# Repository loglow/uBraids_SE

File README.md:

# µBraids SE (uBraids, microBraids) Eurorack [Rev E]

## 8HP Eurorack module | Voltage-controlled digital oscillator

[µBraids SE](http://ubraids-se.com) is a voltage-controlled digital oscillator/sound source in 8HP with a wide range of creative and useful sound generation algorithms (aka models).

This re-engineered Eurorack module updates and simplifies the classic [Mutable Instruments Braids](https://mutable-instruments.net/modules/braids/) design with a custom brilliant orange LED display module protected by a clear acrylic lens, a low-profile rotary encoder, and an added attenuverter.

Fully compatible with upstream Braids firmware. Includes power cable, mounting hardware, and a one-year warranty. Designed and built with care by [Tall Dog Electronics](http://tall-dog.com) in Western Massachusetts. Licensed [CC BY-SA 4.0](https://creativecommons.org/licenses/by-sa/4.0/) open source hardware.

- **Height:** 3U (128.5 mm)
- **Width:** 8HP (40.3 mm)
- **Depth:** 31 mm (with power)
- **+12V:** 100 mA (average)
- **-12V:** 15 mA (average)

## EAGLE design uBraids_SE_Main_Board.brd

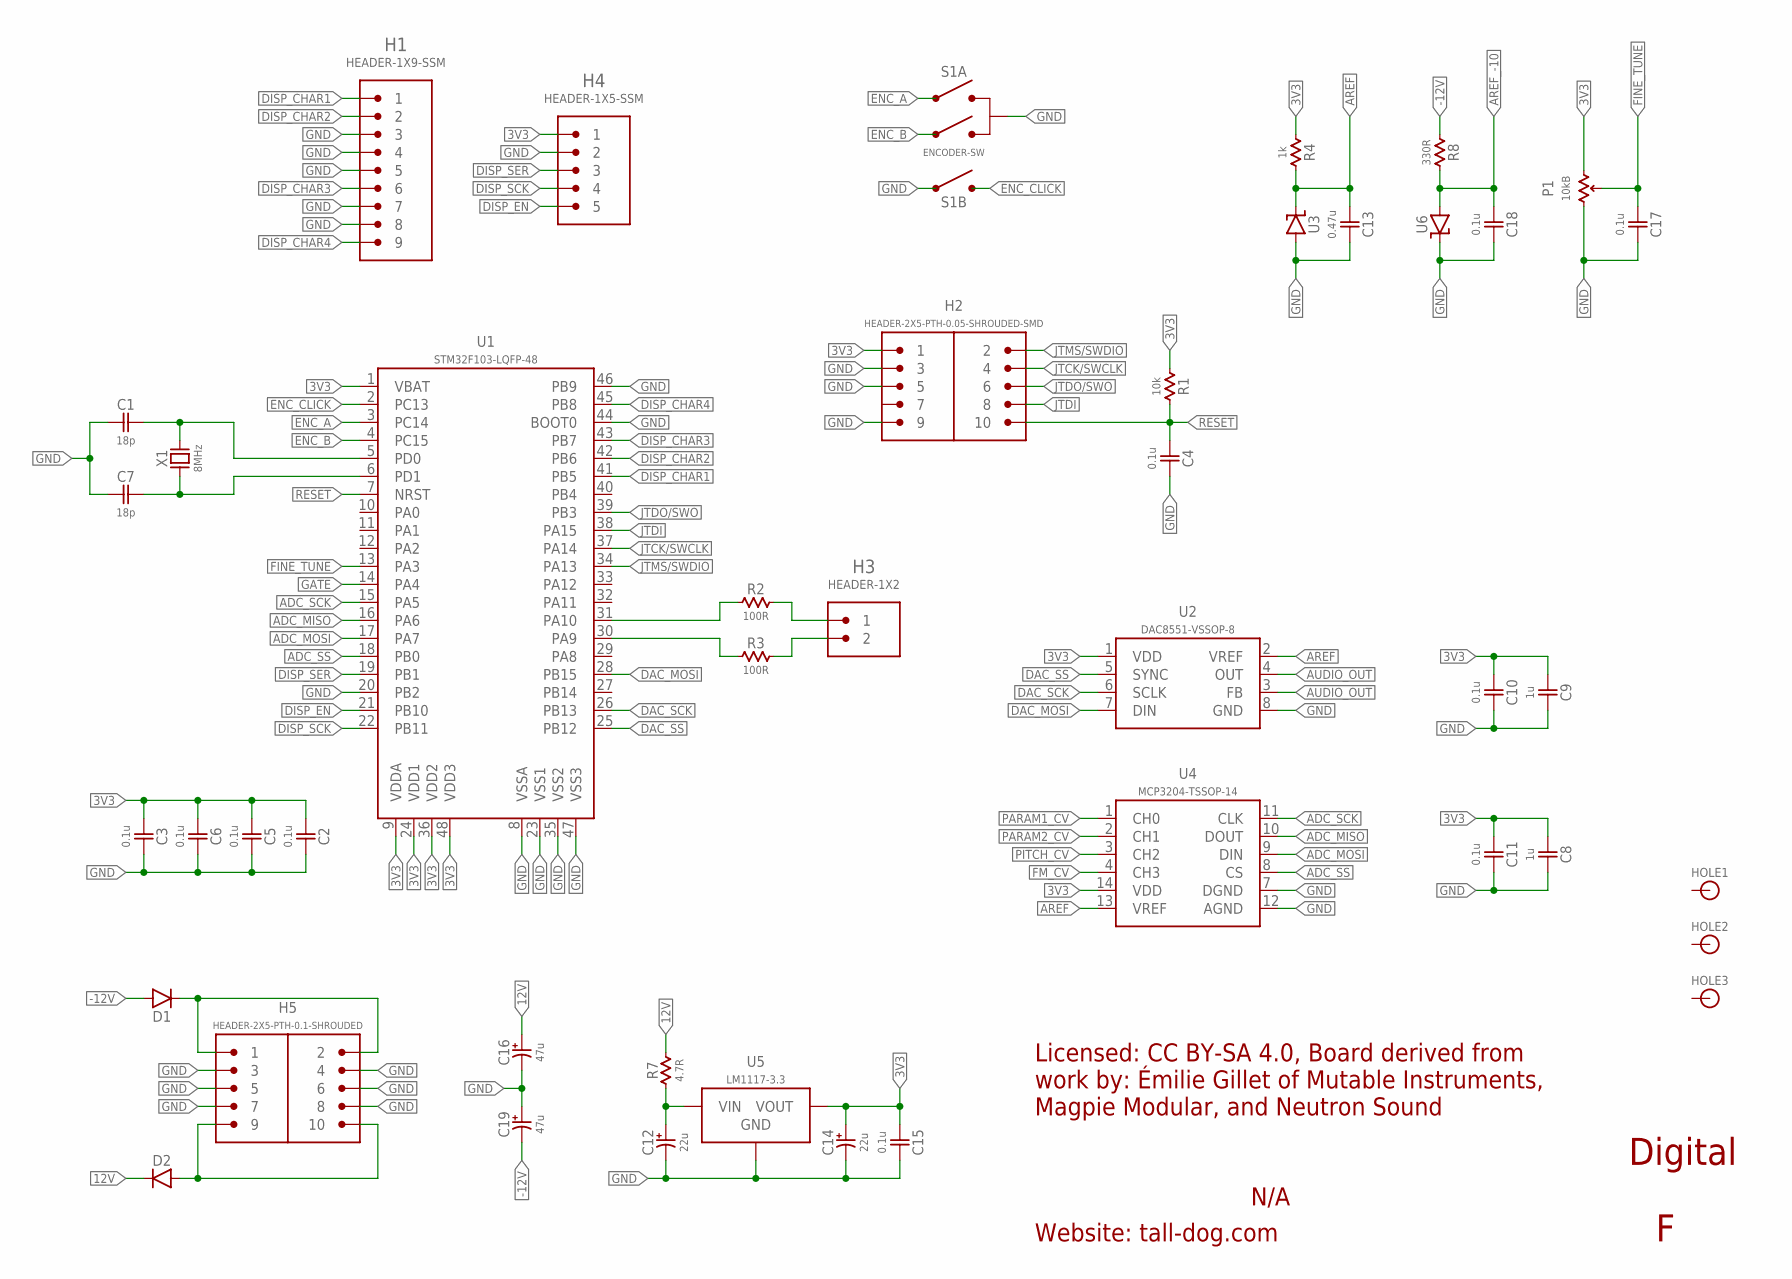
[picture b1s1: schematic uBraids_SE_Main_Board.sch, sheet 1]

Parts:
C1, C7: 18p; 0603-NP
C2, C3, C4, C5, C6, C10, C11, C15, C17, C18: 0.1u; 0603-NP
C8, C9: 1u; 0603-NP
C12, C14: 22u; ELECTRO-SMD-6.6MM
C13: 0.47u; 0603-NP
C16, C19: 47u; ELECTRO-SMD-6.6MM
D1, D2: 1N5819HW; SOD-123
H1: HEADER-1X9-SSM; SSM-109-S-SV-BE
H2: HEADER-2X5-PTH-0.05-SHROUDED-SMD; PTH-0.05-2X5-SHROUDED-SMD
H3: HEADER-1X2; PTH-0.1-1X2
H4: HEADER-1X5-SSM; SSM-105-S-SV-BE
H5: HEADER-2X5-PTH-0.1-SHROUDED; PTH-0.1-2X5-SHROUDED
HOLE1, HOLE2, HOLE3: HOLE; M2.5-HOLE
P1: 10kB; POT
R1: 10k; 0603-NP
R2, R3: 100R; 0603-NP
R4: 1k; 0603-NP
R7: 4.7R; 0805-NP
R8: 330R; 0805-NP
S1: ENCODER-SW; ENCODER-EC12E
U1: STM32F103-LQFP-48; LQFP-48
U2: DAC8551-VSSOP-8; VSSOP-8
U3: LM4040B25; SOT-23
U4: MCP3204-TSSOP-14; TSSOP-14
U5: LM1117-3.3; SOT-223
U6: LM4040B10; SOT-23
X1: 8MHz; CRYSTAL-ABM2

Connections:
3V3: C2.1, C3.1, C5.1, C6.1, C8.1, C9.1, C10.1, C11.1, C14.A (POS), C15.1, H2.1, H4.1, P1.P$1 (E), R1.1, R4.1, U1.1 (VBAT), U1.9 (VDDA), U1.24 (VDD1), U1.36 (VDD2), U1.48 (VDD3), U2.1 (VDD), U4.14 (VDD), U5.2 (VOUT), U5.4 (VOUT); also elsewhere on the board
12V: C16.A (POS), D2.C, R7.2; also elsewhere on the board
12V_BUS: D2.A, H5.9, H5.10
12V_U5: C12.A (POS), R7.1, U5.3 (VIN)
-12V: C19.C (NEG), D1.A, R8.1; also elsewhere on the board
-12V_BUS: D1.C, H5.1, H5.2
ADC_MISO: U1.16 (PA6), U4.10 (DOUT)
ADC_MOSI: U1.17 (PA7), U4.9 (DIN)
ADC_SCK: U1.15 (PA5), U4.11 (CLK)
ADC_SS: U1.18 (PB0), U4.8 (CS)
AREF: C13.1, R4.2, U2.2 (VREF), U3.1 (C), U4.13 (VREF)
AREF_-10: C18.1, R8.2, U6.2 (A); also elsewhere on the board
AUDIO_OUT: U2.3 (FB), U2.4 (OUT); also elsewhere on the board
DAC_MOSI: U1.28 (PB15), U2.7 (DIN)
DAC_SCK: U1.26 (PB13), U2.6 (SCLK)
DAC_SS: U1.25 (PB12), U2.5 (SYNC)
DISP_CHAR1: H1.1, U1.41 (PB5)
DISP_CHAR2: H1.2, U1.42 (PB6)
DISP_CHAR3: H1.6, U1.43 (PB7)
DISP_CHAR4: H1.9, U1.45 (PB8)
DISP_EN: H4.5, U1.21 (PB10)
DISP_SCK: H4.4, U1.22 (PB11)
DISP_SER: H4.3, U1.19 (PB1)
ENC_A: S1.B, U1.3 (PC14)
ENC_B: S1.A, U1.4 (PC15)
ENC_CLICK: S1.E (2), U1.2 (PC13)
FINE_TUNE: C17.1, P1.P$2 (S), U1.13 (PA3)
FM_CV: U4.4 (CH3); also elsewhere on the board
GATE: U1.14 (PA4); also elsewhere on the board
GND: C1.1, C2.2, C3.2, C4.2, C5.2, C6.2, C7.1, C8.2, C9.2, C10.2, C11.2, C12.C (NEG), C13.2, C14.C (NEG), C15.2, C16.C (NEG), C17.2, C18.2, C19.A (POS), H1.3, H1.4, H1.5, H1.7, H1.8, H2.3, H2.5, H2.9, H4.2, H5.3, H5.4, H5.5, H5.6, H5.7, H5.8, P1.P$3 (A), S1.C, S1.D (1), U1.8 (VSSA), U1.20 (PB2), U1.23 (VSS1), U1.35 (VSS2), U1.44 (BOOT0), U1.46 (PB9), U1.47 (VSS3), U2.8 (GND), U3.2 (A), U4.7 (DGND), U4.12 (AGND), U5.1 (GND), U6.1 (C); also elsewhere on the board
JTCK/SWCLK: H2.4, U1.37 (PA14)
JTDI: H2.8, U1.38 (PA15)
JTDO/SWO: H2.6, U1.39 (PB3)
JTMS/SWDIO: H2.2, U1.34 (PA13)
PARAM1_CV: U4.1 (CH0); also elsewhere on the board
PARAM2_CV: U4.2 (CH1); also elsewhere on the board
PD0-XTAL: C1.2, U1.5 (PD0), X1.2
PD1-XTAL: C7.2, U1.6 (PD1), X1.1
PITCH_CV: U4.3 (CH2); also elsewhere on the board
RESET: C4.1, H2.10, R1.2, U1.7 (NRST)
RX: H3.1, R2.2
RX_R: R2.1, U1.31 (PA10)
TX: H3.2, R3.2
TX_R: R3.1, U1.30 (PA9)

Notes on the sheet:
Licensed: CC BY-SA 4.0, Board derived from work by: Émilie Gillet of Mutable Instruments, Magpie Modular, and Neutron Sound
Website: tall-dog.com
N/A
Digital

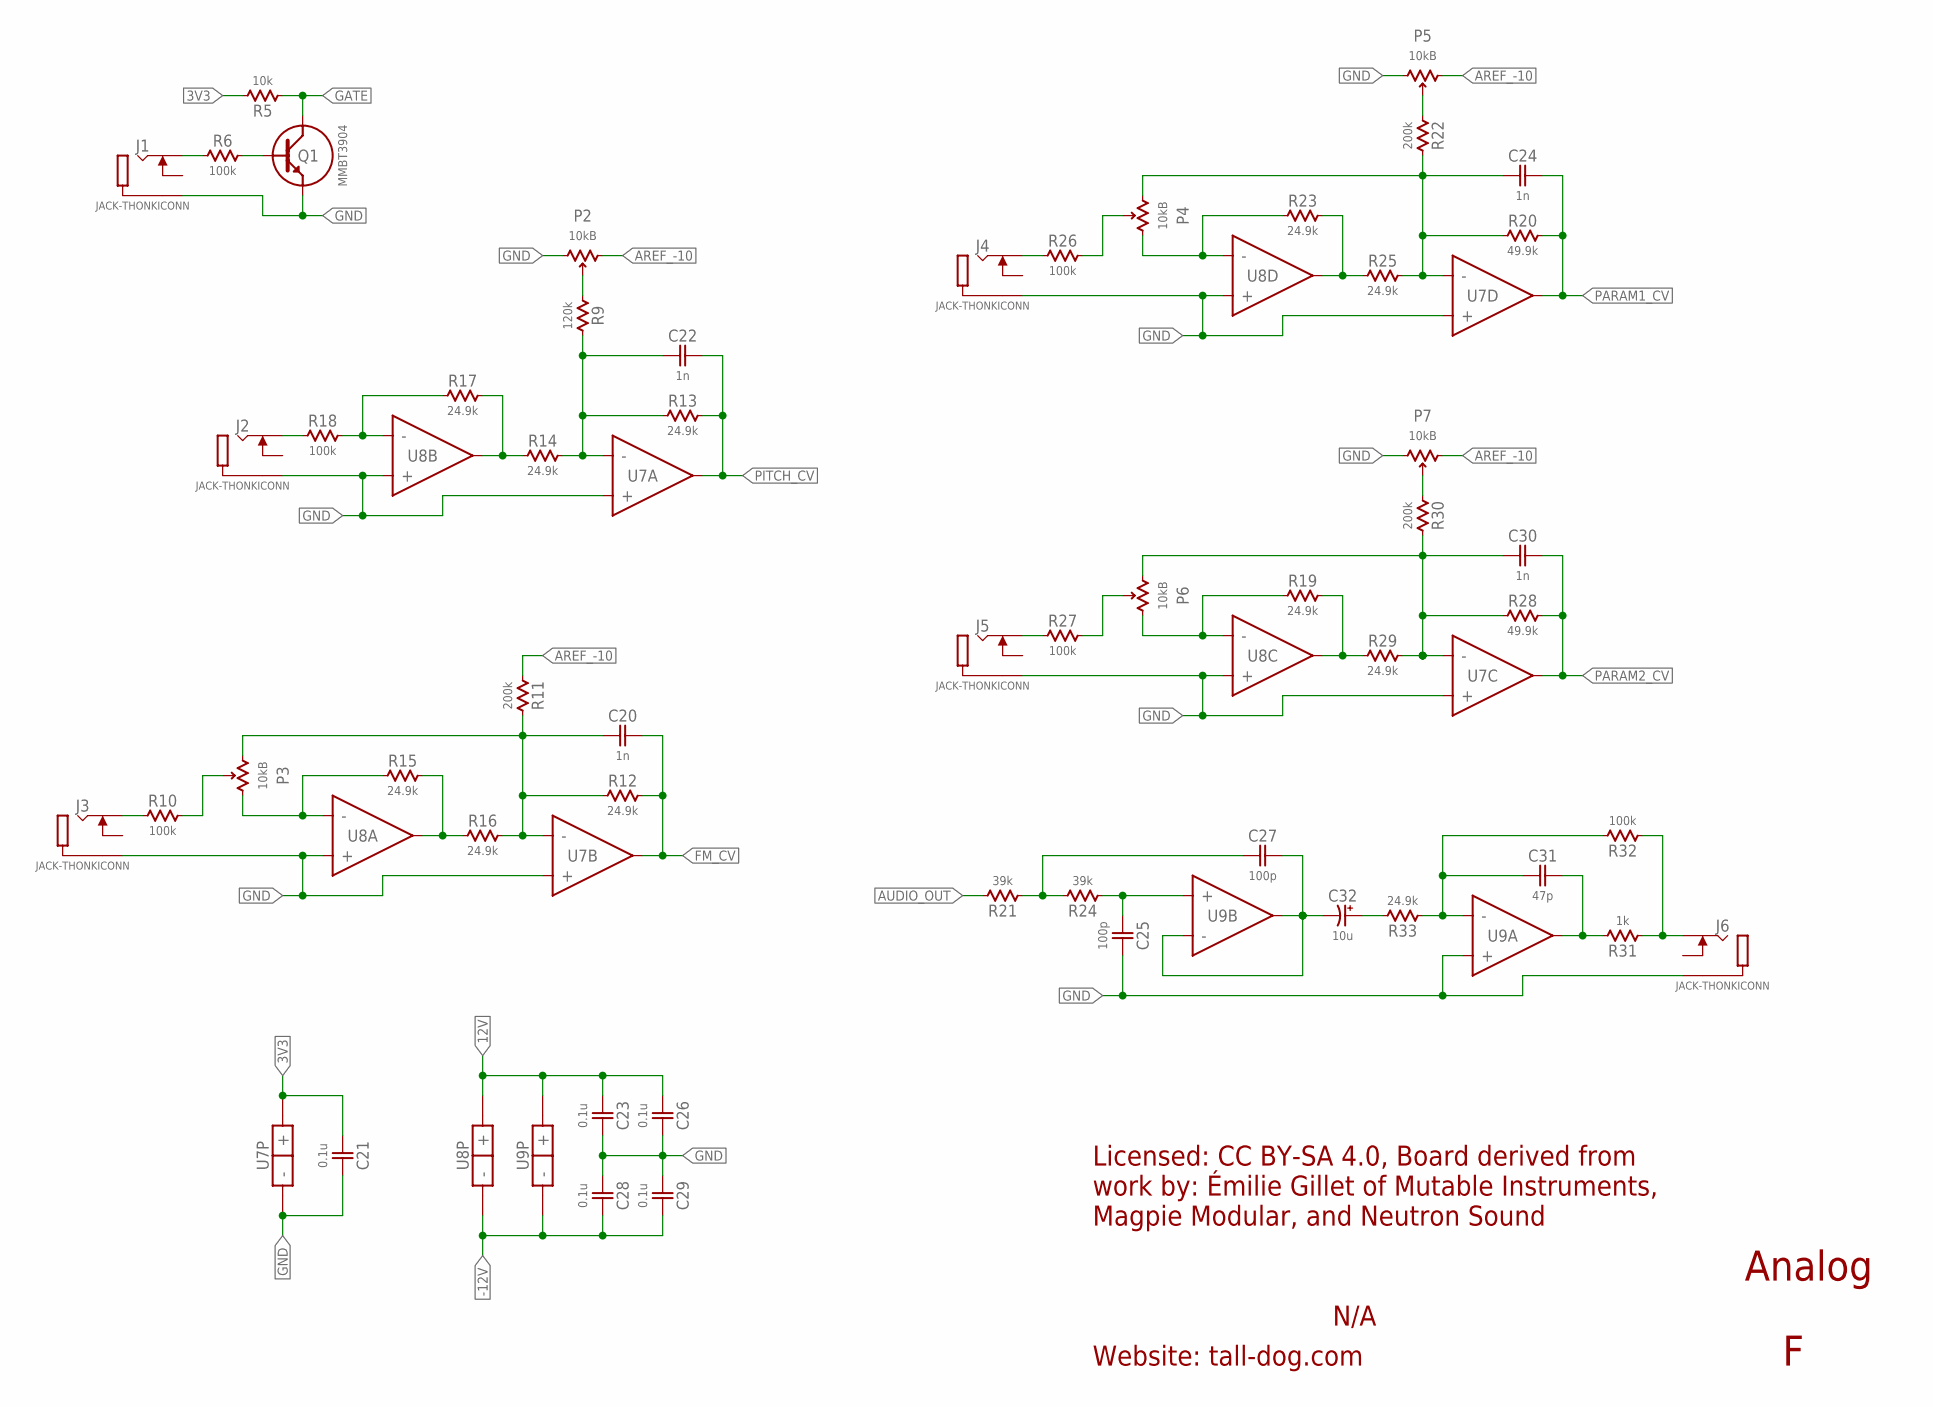
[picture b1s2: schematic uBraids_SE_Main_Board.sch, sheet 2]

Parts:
C20, C22, C24, C30: 1n; 0603-NP
C21, C23, C26, C28, C29: 0.1u; 0603-NP
C25, C27: 100p; 0603-NP
C31: 47p; 0603-NP
C32: 10u; ELECTRO-SMD-4.3MM
J1, J2, J3, J4, J5, J6: JACK-THONKICONN; THONKICONN
P2, P3, P4, P5, P6, P7: 10kB; POT
Q1: MMBT3904; SOT-23
R5: 10k; 0603-NP
R6, R10, R18, R26, R27, R32: 100k; 0603-NP
R9: 120k; 0603-NP
R11, R22, R30: 200k; 0603-NP
R12, R13, R14, R15, R16, R17, R19, R23, R25, R29, R33: 24.9k; 0603-NP
R20, R28: 49.9k; 0603-NP
R21, R24: 39k; 0603-NP
R31: 1k; 0603-NP
U7: MCP6004; TSSOP-14
U8: TL074-TSSOP-14; TSSOP-14
U9: TL072; TSSOP-8

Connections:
3V3: C21.1, R5.2, U7.4 (+); also elsewhere on the board
12V: C23.1, C26.1, U8.4 (+), U9.8 (+); also elsewhere on the board
-12V: C28.2, C29.2, U8.11 (-), U9.4 (-); also elsewhere on the board
AREF_-10: P2.P$1 (E), P5.P$1 (E), P7.P$1 (E), R11.1; also elsewhere on the board
AUDIO_OUT: R21.2; also elsewhere on the board
FM_CV: C20.2, R12.2, U7.7 (OUT); also elsewhere on the board
GATE: Q1.3 (C), R5.1; also elsewhere on the board
GND: C21.2, C23.2, C25.2, C26.2, C28.1, C29.1, J1.P1 (1), J2.P1 (1), J3.P1 (1), J4.P1 (1), J5.P1 (1), J6.P1 (1), P2.P$3 (A), P5.P$3 (A), P7.P$3 (A), Q1.2 (E), U7.3 (+), U7.5 (+), U7.10 (+), U7.11 (-), U7.12 (+), U8.3 (+), U8.5 (+), U8.10 (+), U8.12 (+), U9.3 (+); also elsewhere on the board
unnamed: P6.P$2 (S), R27.2
unnamed: C24.1, P4.P$3 (A), R20.1, R22.2, R25.2, U7.13 (-)
unnamed: R14.1, R17.2, U8.7 (OUT)
unnamed: P2.P$2 (S), R9.1
unnamed: J2.P3 (3), R18.1
unnamed: C22.1, R9.2, R13.1, R14.2, U7.2 (-)
unnamed: R17.1, R18.2, U8.6 (-)
unnamed: J3.P3 (3), R10.1
unnamed: J4.P3 (3), R26.1
unnamed: P3.P$2 (S), R10.2
unnamed: P4.P$1 (E), R23.1, U8.13 (-)
unnamed: R23.2, R25.1, U8.14 (OUT)
unnamed: P3.P$1 (E), R15.1, U8.2 (-)
unnamed: R15.2, R16.1, U8.1 (OUT)
unnamed: C20.1, P3.P$3 (A), R11.2, R12.1, R16.2, U7.6 (-)
unnamed: J1.P3 (3), R6.1
unnamed: R19.2, R29.1, U8.8 (OUT)
unnamed: J5.P3 (3), R27.1
unnamed: P5.P$2 (S), R22.1
unnamed: P4.P$2 (S), R26.2
unnamed: P6.P$1 (E), R19.1, U8.9 (-)
unnamed: P7.P$2 (S), R30.1
unnamed: Q1.1 (B), R6.2
unnamed: C27.2, C32.C (NEG), U9.6 (-), U9.7 (OUT)
unnamed: C32.A (POS), R33.2
unnamed: C25.1, R24.1, U9.5 (+)
unnamed: C30.1, P6.P$3 (A), R28.1, R29.2, R30.2, U7.9 (-)
unnamed: C27.1, R21.1, R24.2
unnamed: J6.P3 (3), R31.1, R32.1
unnamed: C31.2, R31.2, U9.1 (OUT)
unnamed: C31.1, R32.2, R33.1, U9.2 (-)
PARAM1_CV: C24.2, R20.2, U7.14 (OUT); also elsewhere on the board
PARAM2_CV: C30.2, R28.2, U7.8 (OUT); also elsewhere on the board
PITCH_CV: C22.2, R13.2, U7.1 (OUT); also elsewhere on the board

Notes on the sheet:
Licensed: CC BY-SA 4.0, Board derived from work by: Émilie Gillet of Mutable Instruments, Magpie Modular, and Neutron Sound
Website: tall-dog.com
Analog
N/A

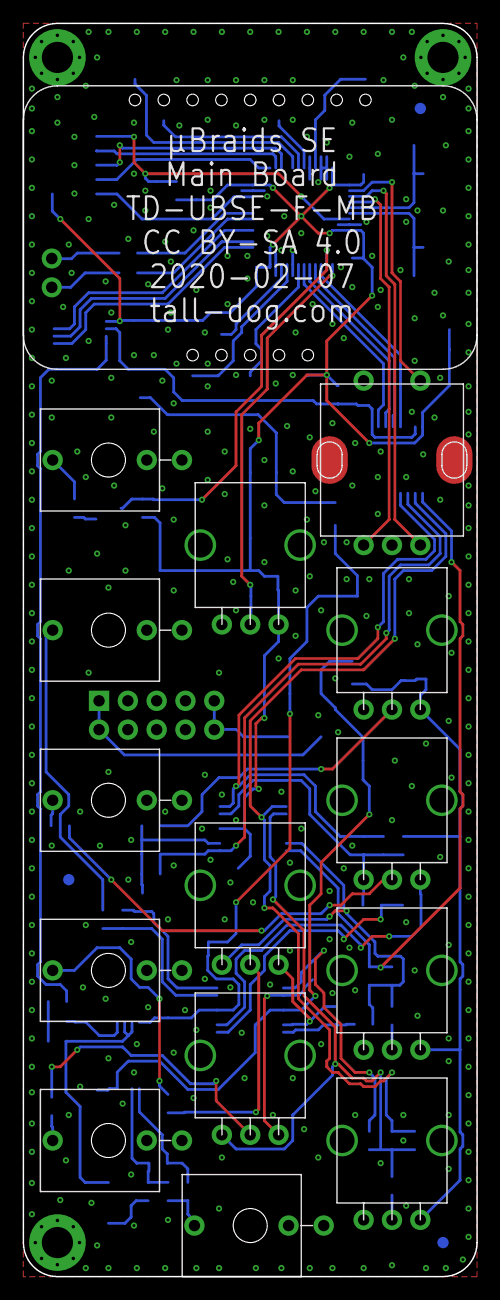
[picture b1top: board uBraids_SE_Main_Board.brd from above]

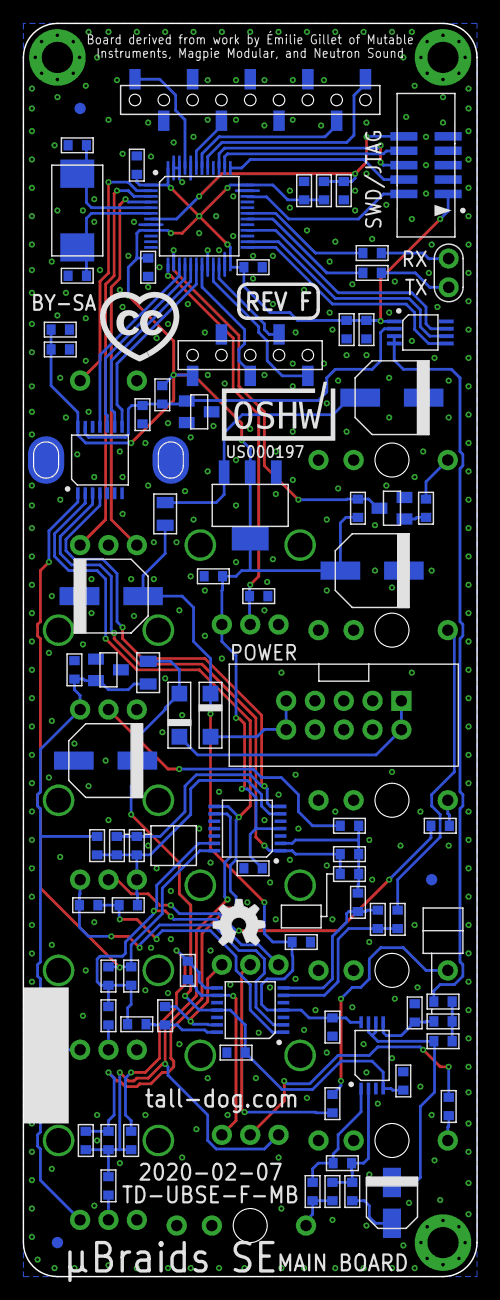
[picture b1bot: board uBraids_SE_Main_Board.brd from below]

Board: 2 copper layers, 40.0 x 110.5 mm, 108 parts (90 on the bottom side), 75 nets.

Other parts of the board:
A1: DISPLAY-MODULE-OUTLINE
U$1, U$6, U$7: FIDUCIAL
U$2: LOGO-REV
U$3: LOGO-OSH
U$4: LOGO-CC
U$8: LOGO-OSHW

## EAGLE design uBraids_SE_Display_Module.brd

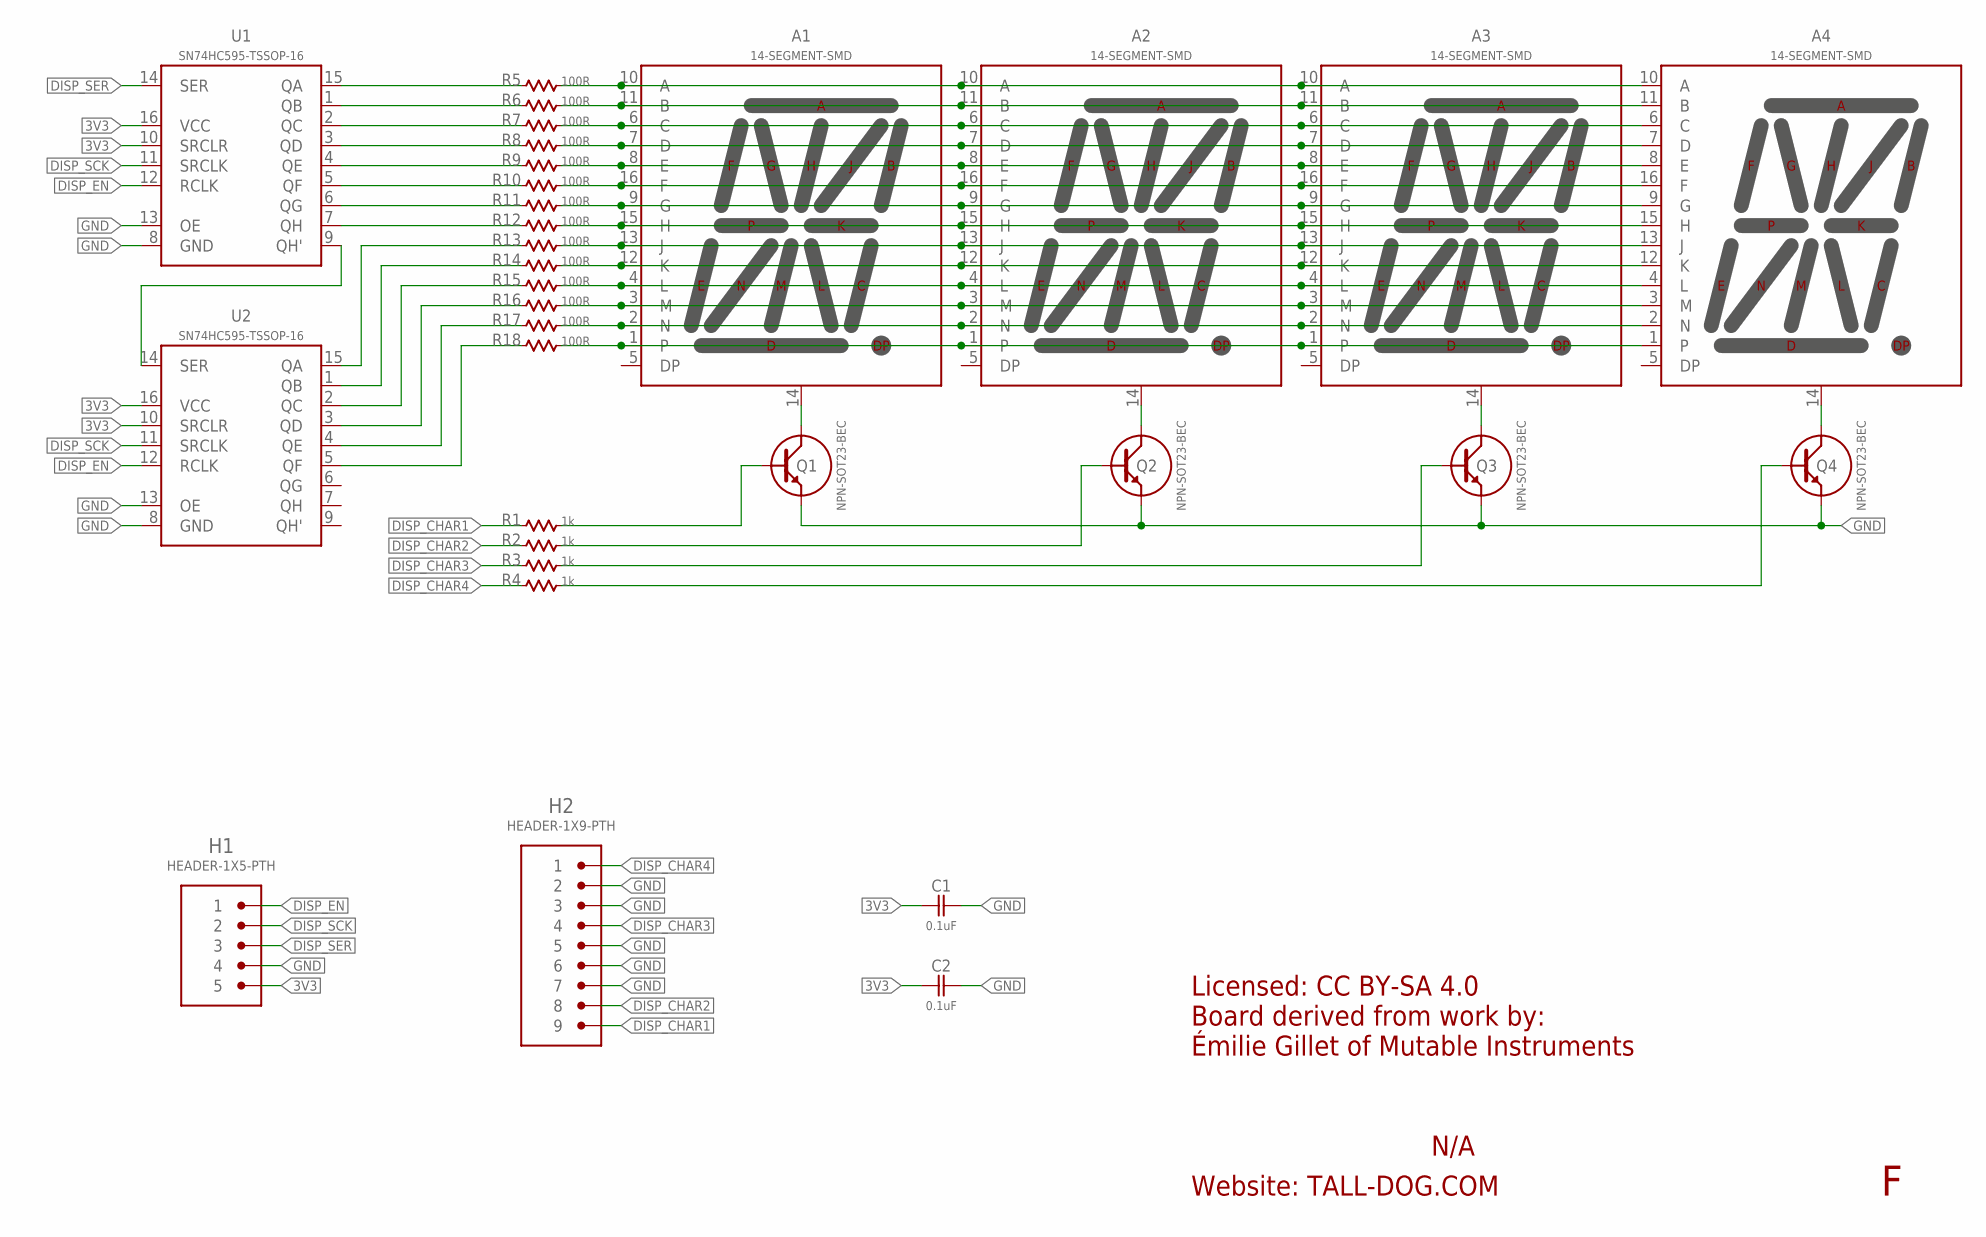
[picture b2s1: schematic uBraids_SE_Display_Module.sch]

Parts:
A1, A2, A3, A4: 14-SEGMENT-SMD; 14-SEGMENT
C1, C2: 0.1uF; 0603-NP
H1: HEADER-1X5-PTH; PTH-0.1-1X5
H2: HEADER-1X9-PTH; PTH-0.1-1X9
Q1, Q2, Q3, Q4: NPN-SOT23-BEC; SOT-23
R1, R2, R3, R4: 1k; 0603-NP
R5, R6, R7, R8, R9, R10, R11, R12, R13, R14, R15, R16, R17, R18: 100R; 0603-NP
U1, U2: SN74HC595-TSSOP-16; TSSOP-16

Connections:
3V3: C1.1, C2.1, H1.5, U1.10 (SRCLR), U1.16 (VCC), U2.10 (SRCLR), U2.16 (VCC)
A: A1.10 (A), A2.10 (A), A3.10 (A), A4.10 (A), R5.2
A1C: A1.14 (CATHODE), Q1.3 (C)
A2C: A2.14 (CATHODE), Q2.3 (C)
A3C: A3.14 (CATHODE), Q3.3 (C)
A4C: A4.14 (CATHODE), Q4.3 (C)
B: A1.11 (B), A2.11 (B), A3.11 (B), A4.11 (B), R6.2
C: A1.6 (C), A2.6 (C), A3.6 (C), A4.6 (C), R7.2
D: A1.7 (D), A2.7 (D), A3.7 (D), A4.7 (D), R8.2
DISP_CHAR1: H2.9, R1.1
DISP_CHAR2: H2.8, R2.1
DISP_CHAR3: H2.4, R3.1
DISP_CHAR4: H2.1, R4.1
DISP_EN: H1.1, U1.12 (RCLK), U2.12 (RCLK)
DISP_SCK: H1.2, U1.11 (SRCLK), U2.11 (SRCLK)
DISP_SER: H1.3, U1.14 (SER)
E: A1.8 (E), A2.8 (E), A3.8 (E), A4.8 (E), R9.2
F: A1.16 (F), A2.16 (F), A3.16 (F), A4.16 (F), R10.2
G: A1.9 (G), A2.9 (G), A3.9 (G), A4.9 (G), R11.2
GND: C1.2, C2.2, H1.4, H2.2, H2.3, H2.5, H2.6, H2.7, Q1.2 (E), Q2.2 (E), Q3.2 (E), Q4.2 (E), U1.8 (GND), U1.13 (OE), U2.8 (GND), U2.13 (OE)
H: A1.15 (H), A2.15 (H), A3.15 (H), A4.15 (H), R12.2
J: A1.13 (J), A2.13 (J), A3.13 (J), A4.13 (J), R13.2
K: A1.12 (K), A2.12 (K), A3.12 (K), A4.12 (K), R14.2
L: A1.4 (L), A2.4 (L), A3.4 (L), A4.4 (L), R15.2
M: A1.3 (M), A2.3 (M), A3.3 (M), A4.3 (M), R16.2
N: A1.2 (N), A2.2 (N), A3.2 (N), A4.2 (N), R17.2
P: A1.1, A2.1, A3.1, A4.1, R18.2
Q1B: Q1.1 (B), R1.2
Q2B: Q2.1 (B), R2.2
Q3B: Q3.1 (B), R3.2
Q4B: Q4.1 (B), R4.2
RA: R5.1, U1.15 (QA)
RB: R6.1, U1.1 (QB)
RC: R7.1, U1.2 (QC)
RD: R8.1, U1.3 (QD)
RE: R9.1, U1.4 (QE)
RF: R10.1, U1.5 (QF)
RG: R11.1, U1.6 (QG)
RH: R12.1, U1.7 (QH)
RJ: R13.1, U2.15 (QA)
RK: R14.1, U2.1 (QB)
RL: R15.1, U2.2 (QC)
RM: R16.1, U2.3 (QD)
RN: R17.1, U2.4 (QE)
RP: R18.1, U2.5 (QF)
U1-U2: U1.9 (QH'), U2.14 (SER)

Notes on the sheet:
Licensed: CC BY-SA 4.0 Board derived from work by: Émilie Gillet of Mutable Instruments
Website: TALL-DOG.COM
N/A

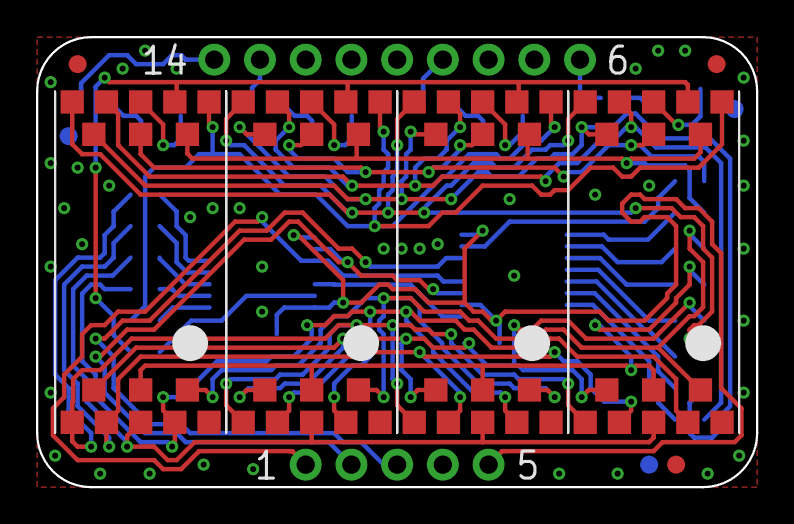
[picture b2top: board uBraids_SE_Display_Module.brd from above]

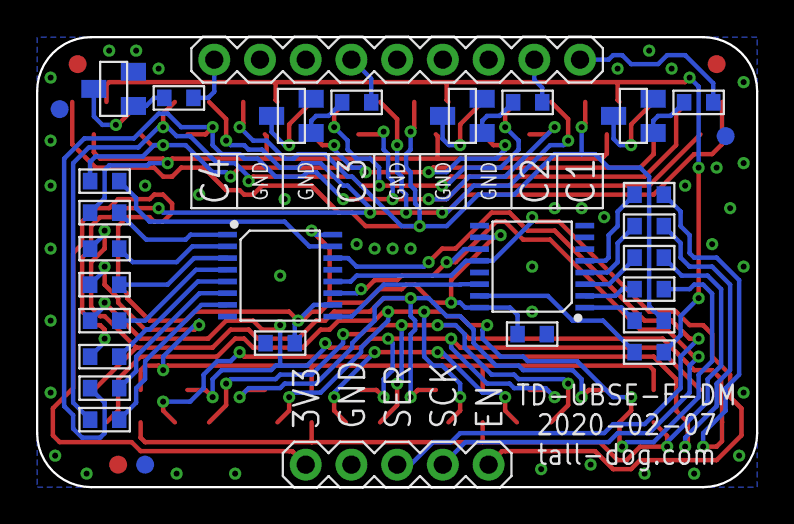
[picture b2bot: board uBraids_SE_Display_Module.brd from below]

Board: 2 copper layers, 40.0 x 25.0 mm, 38 parts (31 on the bottom side), 46 nets.

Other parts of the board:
U$1, U$2, U$3, U$4, U$5, U$6: FIDUCIAL

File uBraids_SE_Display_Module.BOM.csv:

Line,Reference,Quantity,Description,Package,Manufacturer,Part Number,Digi-Key P/N
1,"A1,A2,A3,A4",4,"DISPLAY 610NM ORN 1DIG 0.4"" SMD",N/A,Kingbright,ACPSC04-41SEKWA,ACPSC04-41SEKWA-ND
2,"C1,C2",2,CAP CER 0.1UF 50V X7R 0603,0603,Samsung,CL10B104JB8NNNC,1276-1033-1-ND 
3,H1,1,".025"" BOARD SPACERS",N/A,Samtec,DW-05-07-T-S-200,DW-05-07-T-S-200-ND
4,H2,1,".025"" BOARD SPACERS",N/A,Samtec,DW-09-07-T-S-200,DW-09-07-T-S-200-ND
5,"Q1,Q2,Q3,Q4",4,TRANS NPN 40V 0.2A SC70-3,SOT-323,Diodes Incorporated,MMST3904-7-F,MMST3904-FDICT-ND
6,"R1,R2,R3,R4",4,RES SMD 1K OHM 1% 1/10W 0603,0603,Panasonic,ERJ-3EKF1001V,P1.00KHCT-ND
7,"R5,R6,R7,R8,R9,R10,R11,R12,R13,R14,R15,R16,R17,R18",14,RES SMD 100 OHM 1% 1/10W 0603,0603,Panasonic,ERJ-3EKF1000V,P100HCT-ND
8,"U1,U2",2,IC 8BIT SHIFT REGISTER 16-TSSOP,TSSOP-16,Texas Instruments,SN74HC595PWR,296-23258-1-ND

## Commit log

2017-10-23 revision C first pass, primarily to address rail clearance
2017-10-24 removed additional 0.5 mm from main board, adjusted panel to match
2017-10-24 updated BOMs for revision C
2017-10-24 added component library file
2017-10-25 prep for production of revision C
2017-10-25 git ignore
2017-12-13 added hardware BOM and the two 3D printed part models
2017-12-31 very minor changes for new production run
2018-01-25 added front panel template in Adobe Illustrator format
2018-11-09 Rename uBraids_SE.lbr to uBraids_SE_Library.lbr
2018-11-09 Rename uBraids_SE_Display_Module.BOM.csv to uBraids_SE_Display_Module_BOM.csv
2018-11-09 Rename uBraids_SE_Hardware.BOM.csv to uBraids_SE_Hardware_BOM.csv
2018-11-09 Rename uBraids_SE_Main_Board.BOM.csv to uBraids_SE_Main_Board_BOM.csv
2018-11-09 removing outdated files
2018-11-09 adding new files
2018-11-09 update for Revision E production
2021-03-23 Revision F
